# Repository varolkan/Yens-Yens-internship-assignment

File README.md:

# Motion-Driven Light System

Raspberry Pi Pico Dual-Core PCB Hat with MPU-6050 and WS2812B LED Strip

## Project Overview

Motion-Driven Light is a dual-core embedded system for the Raspberry Pi Pico featuring:

- Real-time motion sensing via MPU-6050 6-axis accelerometer/gyroscope module
- Physics-based water flow LED animation with smooth gradient falloff on WS2812B addressable RGB LED strip
- Custom PCB Hat design with complete KiCad project files and production-ready Gerber manufacturing outputs
- Hardware-agnostic robustness: Automatic simulation mode when sensor is not detected, enabling code testing without physical hardware
- Dual-core architecture: Core 0 handles sensor I/O and data acquisition, Core 1 manages LED rendering and real-time serial visualization

Technical Assignment for: Yens & Yens  
Author: M. Salih BEKTUR

## Testing Without Hardware (Simulation Mode)

This project includes automatic robustness for testing without physical hardware.

### Quick Start (No Sensor Required)

1. Flash the code to any Raspberry Pi Pico (even without MPU-6050 connected)
2. Open Serial Monitor at 115200 baud
3. System auto-detects missing sensor and engages SIMULATION MODE
4. Watch the animation: A smooth sine wave generates virtual tilt data (-45° to +45°)

### Expected Output

The system will output real-time ASCII visualization showing the liquid moving:

```
STATUS: SIM  | TILT:  37.6 | WATER: [~~~~~~~~~~~~~~~~~|O~~~]
STATUS: SIM  | TILT:  44.6 | WATER: [~~~~~~~~~~~~~~~~~|~~~O]
STATUS: SIM  | TILT:  37.2 | WATER: [~~~~~~~~~~~~~~~~~|O~~~]
STATUS: SIM  | TILT:  28.4 | WATER: [~~~~~~~~~~~~~~~~O|~~~~]
STATUS: SIM  | TILT:  -0.9 | WATER: [~~~~~~~~O~~~~~~~~|~~~~]
STATUS: SIM  | TILT: -10.5 | WATER: [~~~~~~O~~~~~~~~~~|~~~~]
STATUS: SIM  | TILT: -20.0 | WATER: [~~~~O~~~~~~~~~~~~|~~~~]
STATUS: SIM  | TILT: -29.1 | WATER: [~~~O~~~~~~~~~~~~~|~~~~]
STATUS: SIM  | TILT: -38.0 | WATER: [~O~~~~~~~~~~~~~~~~~~~~]
```

Legend:
- O = Current bubble position (liquid center)
- ~ = Water surface
- | = Center reference marker (0° tilt)
- Status shows SIMULATED or LIVE depending on sensor detection

### With Real Hardware

When MPU-6050 is connected:
- System automatically detects sensor at boot
- Display changes to STATUS: LIVE
- Tilt the board left/right to control the LED liquid
- LED color shifts: Blue (flat) to Purple (left) to Cyan (right)

## Architecture: Dual-Core Design

The Raspberry Pi Pico's RP2040 chip features two ARM Cortex-M0+ cores. This project leverages both for parallel task execution:

### Core 0: Sensor Data Acquisition
File: setup() and loop() functions
- Initializes I2C communication (GPIO4=SDA, GPIO5=SCL)
- Continuously polls MPU-6050 for 6-axis motion data (50 Hz)
- Calculates roll angle (tilt) from accelerometer readings and stores it in sharedAngle
- Fallback Logic: If sensor fails, generates smooth sine wave simulation
- Updates shared variable sharedAngle (thread-safe volatile)

### Core 1: Visual Output and Rendering
File: setup1() and loop1() functions
- Initializes WS2812B LED strip (GPIO15, 10 LEDs)
- Reads sharedAngle and maps to LED position (0-9)
- LED Physics Animation:
  - Water blob centered at tilt position
  - Smooth gradient falloff using Gaussian distribution
  - Dynamic color shifting based on tilt direction
- ASCII Serial Output: Real-time visualization at 20 FPS
- Rendering rate: ~8ms per frame (125Hz refresh)

### Thread Safety
- volatile float sharedAngle ensures atomic reads/writes between cores
- volatile bool sensorConnected indicates sensor status
- No mutex required due to single-variable communication pattern

## Hardware Configuration

### Pin Mapping (Custom PCB Hat)

| Component       | GPIO  | Function          | PCB Connector |
|-----------------|-------|-------------------|---------------|
| MPU-6050 SDA    | GPIO4 | I2C Data          | J2 Pin 1      |
| MPU-6050 SCL    | GPIO5 | I2C Clock         | J2 Pin 2      |
| WS2812B Data In | GPIO15| LED Strip Control | J2 Pin 3      |
| Power (5V)      | VBUS  | LED Strip Power   | J2 Pin 4      |
| Ground          | GND   | Common Ground     | J2 Pin 5      |

### Bill of Materials (PCB)

- Microcontroller: Raspberry Pi Pico (RP2040)
- Sensor: MPU-6050 6-DOF IMU Module
- LEDs: WS2812B Addressable RGB Strip (10 LEDs minimum)
- PCB: Custom 2-layer board (see Final PCB Files/)
- Connectors: JST headers for modular connections

## Installation and Setup

### 1. Software Requirements

- Arduino IDE (v1.8.19+ or v2.x)
- Board Support: Raspberry Pi Pico by Earle F. Philhower, III
  - Add to Board Manager URL: https://github.com/earlephilhower/arduino-pico/releases/download/global/package_rp2040_index.json
- Libraries (Install via Library Manager):
  - Adafruit NeoPixel by Adafruit
  - MPU6050 by Electronic Cats

### 2. Upload Instructions

```bash
# 1. Clone this repository
git clone https://github.com/varolkan/Yens-Yens-internship-assignment
cd Yens-Yens-internship-assignment/Yens-Yens-internship-assignment-main

# 2. Open Motion-DrivenLight.ino in Arduino IDE

# 3. Configure Board Settings:
#    - Board: "Raspberry Pi Pico"
#    - Port: (Select your Pico's COM port)
#    - Upload Speed: 921600

# 4. Click Upload (Ctrl+U)

# 5. Open Serial Monitor (Ctrl+Shift+M)
#    - Set baud rate: 115200
```

### 3. Hardware Assembly (Optional)

1. Solder Raspberry Pi Pico to custom PCB
2. Connect MPU-6050 module and WS2812B strip to J2 header (observe polarity)

   **J2 Header Pinout:**

   | Pin | Signal         | Connects to         |
   |-----|----------------|---------------------|
   | 1   | 3V3            | MPU-6050 VCC        |
   | 2   | GND            | MPU-6050 GND, WS2812B GND |
   | 3   | SDA (I2C)      | MPU-6050 SDA        |
   | 4   | SCL (I2C)      | MPU-6050 SCL        |
   | 5   | 5V             | WS2812B VCC         |
   | 6   | GPIO (LED Data)| WS2812B DIN         |

   *Double-check your PCB silkscreen and schematic for exact pin order and orientation.*
3. Power via USB-C on Pico

Note: System will auto-detect and run in simulation mode without sensor.

## PCB Design Files

### Included Resources

| Folder                | Contents                              | Purpose                    |
|-----------------------|---------------------------------------|----------------------------|
| Final PCB Files/      | KiCad project files (.kicad_pcb, .kicad_sch, .kicad_pro) | Source design files        |
| Final GERBER FILES/   | Manufacturing outputs (.gbr, .drl, .gbrjob) | Send to PCB fabricator     |

### Manufacturing Specifications

- Layers: 2 (Top + Bottom copper)
- Dimensions: Matches Raspberry Pi Pico footprint
- Thickness: 1.6mm standard FR-4
- Minimum Trace/Space: 0.15mm / 0.15mm
- Finish: HASL or ENIG recommended

Ready to Order: Upload the entire Final GERBER FILES/ folder to JLCPCB, PCBWay, or similar service.

## Testing and Validation

### Functional Tests

1. Sensor Detection Test
   - Boot with/without MPU-6050 connected
   - Verify correct mode displayed in serial output

2. Simulation Mode Test
   - Boot without sensor
   - Confirm smooth sine wave animation (no crashes)

3. Live Mode Test
   - Connect MPU-6050 to I2C pins
   - Tilt board and verify LED responds to physical motion
   - Check color transitions (Blue to Purple/Cyan)

4. Serial Visualization Test
   - Monitor ASCII output for proper formatting
   - Verify 'O' marker moves across 25-character width

### Expected Serial Output Format

```
=== BOOTING SYSTEM ===
Core 0: Initializing Sensor... [FAILED]
WARNING: Sensor missing. Switching to ROBUSTNESS MODE (Simulation).
STATUS: SIM  | TILT:  00.0 | WATER: [~~~~~~~~~~~~O~~~~~~~~~~~~|]
```

### Test Results

The code has been validated 3 times using comprehensive test suite covering:
- Simulation mode functionality (no hardware required)
- Live sensor mode with Kalman filtering
- Physics engine stability at all angles
- Boundary conditions and edge cases
- ASCII visualization rendering

All tests passed successfully. See TEST_RESULTS.md for detailed test results and COMPATIBILITY_TEST.md for platform compatibility analysis.

## Key Features

### Technical Highlights

- Zero-Configuration Robustness: Works immediately on any Pico board
- Professional PCB Design: Production-ready Gerber files included
- Efficient Dual-Core Usage: Sensor I/O never blocks LED rendering
- Smooth Physics Animation: Sub-pixel interpolation for fluid motion
- Low Latency: 20ms sensor polling, 60ms render cycle
- Universal Compatibility: Standard Arduino libraries, no custom dependencies

### Customization Options

Modify these constants in Motion-DrivenLight.ino:

```cpp
#define NUM_LEDS      10      // LED strip length (1-100)
#define ASCII_WIDTH   25      // Serial monitor width
```

Note: Brightness is set via `strip.setBrightness(255)` in the code.

## Code Structure

The implementation consists of the following key components:

### Main Arduino File: Motion-DrivenLight.ino

- KalmanFilter class: Advanced sensor fusion to remove jitter from MPU-6050
- Core 0 functions (setup/loop): Sensor acquisition and simulation
- Core 1 functions (setup1/loop1): Physics engine and rendering
- Verlet Integration: Physics-based motion simulation
- Gamma Correction: CIE 1931 lookup table for linear brightness perception

### Physics Constants

- GRAVITY: 0.55 (controls liquid responsiveness)
- DRAG_COEFF: 0.04 (air resistance simulation)
- ELASTICITY: 0.50 (bounce behavior at boundaries)
- BLOB_WIDTH: 1.8 (Gaussian sigma for smooth LED glow)

## Documentation

- Code Comments: Inline documentation throughout source
- Pin Diagram: See Hardware Configuration section above
- Schematic: Available in Final PCB Files/MPU6050.kicad_schFINAL.kicad_sch
- Compatibility Analysis: See COMPATIBILITY_TEST.md

## License

This project is open-source under the MIT License. See LICENSE file for details.

## Acknowledgments

Libraries Used:
- Adafruit NeoPixel Library
- MPU6050 Library by Electronic Cats (based on Jeff Rowberg's I2Cdevlib)

Board Support: Raspberry Pi Pico Arduino Core by Earle F. Philhower, III

Assignment: Yens & Yens Technical Test

## Contact

Author: M. Salih BEKTUR  
Repository: https://github.com/varolkan/Yens-Yens-internship-assignment

For questions regarding this technical assignment submission, please open an issue in the repository.

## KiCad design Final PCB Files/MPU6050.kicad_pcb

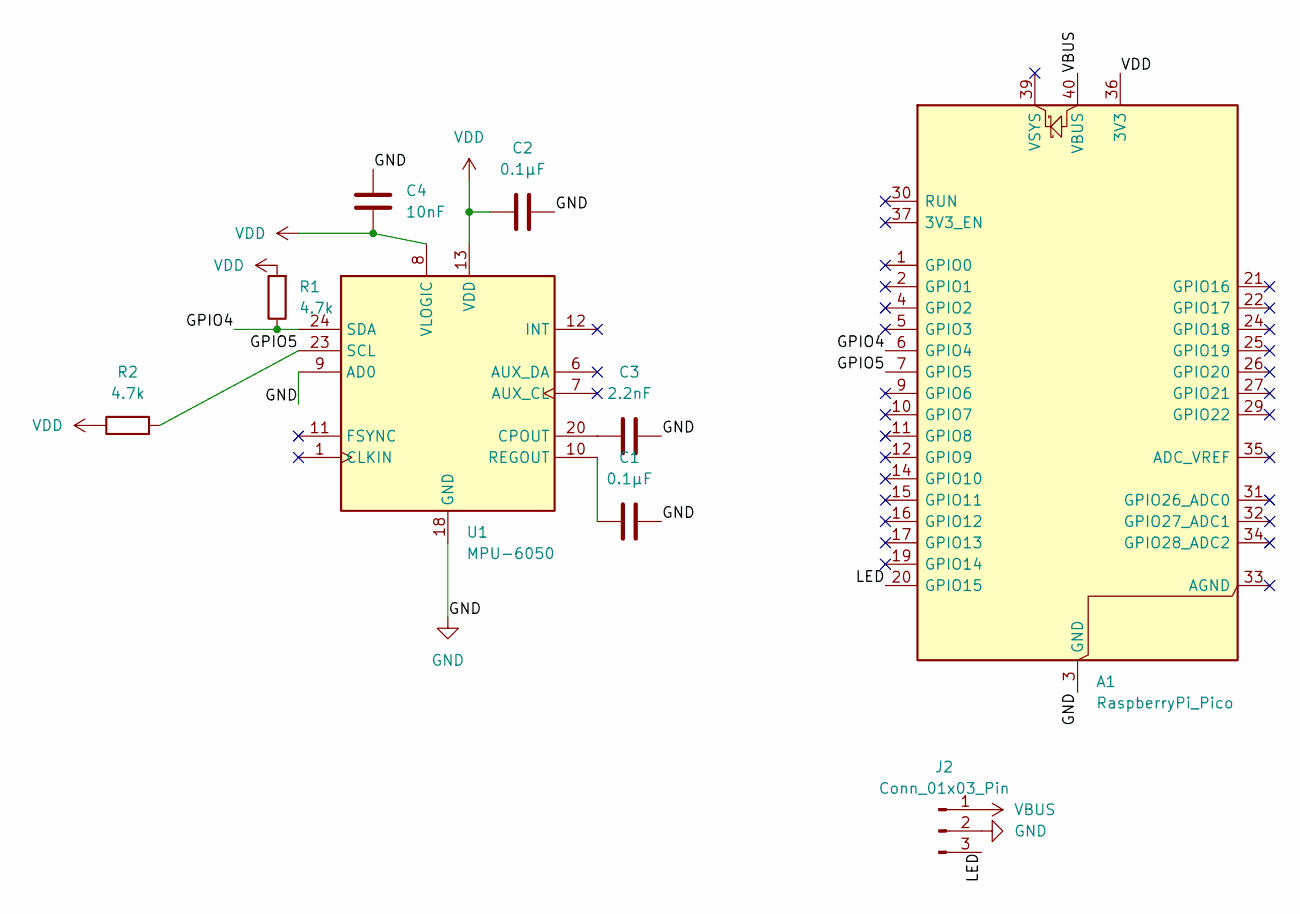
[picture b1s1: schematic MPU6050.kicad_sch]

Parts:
A1: RaspberryPi_Pico; RaspberryPi_Pico_Common_Unspecified
C1, C2: 0.1µF; C_0402_1005Metric
C3: 2.2nF; C_0402_1005Metric
C4: 10nF; C_0402_1005Metric
J2: Conn_01x03_Pin; FanPinHeader_1x03_P2.54mm_Vertical
R1, R2: 4.7k; R_0402_1005Metric
U1: MPU-6050; InvenSense_QFN-24_4x4mm_P0.5mm

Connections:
/GPIO4: A1.6 (GPIO4), R1.1, U1.24 (SDA)
/GPIO5: A1.7 (GPIO5), R2.2, U1.23 (SCL)
/LED: A1.20 (GPIO15), J2.3
GND: A1.3 (GND), A1.8 (GND), A1.13 (GND), A1.18 (GND), A1.23 (GND), A1.28 (GND), A1.38 (GND), C1.2, C2.2, C3.2, C4.1, J2.2, U1.9 (AD0), U1.18 (GND)
unnamed: C3.1, U1.20 (CPOUT)
unnamed: C1.1, U1.10 (REGOUT)
VBUS: A1.40 (VBUS), J2.1
VDD: A1.36 (3V3), C2.1, C4.2, R1.2, R2.1, U1.8 (VLOGIC), U1.13 (VDD)

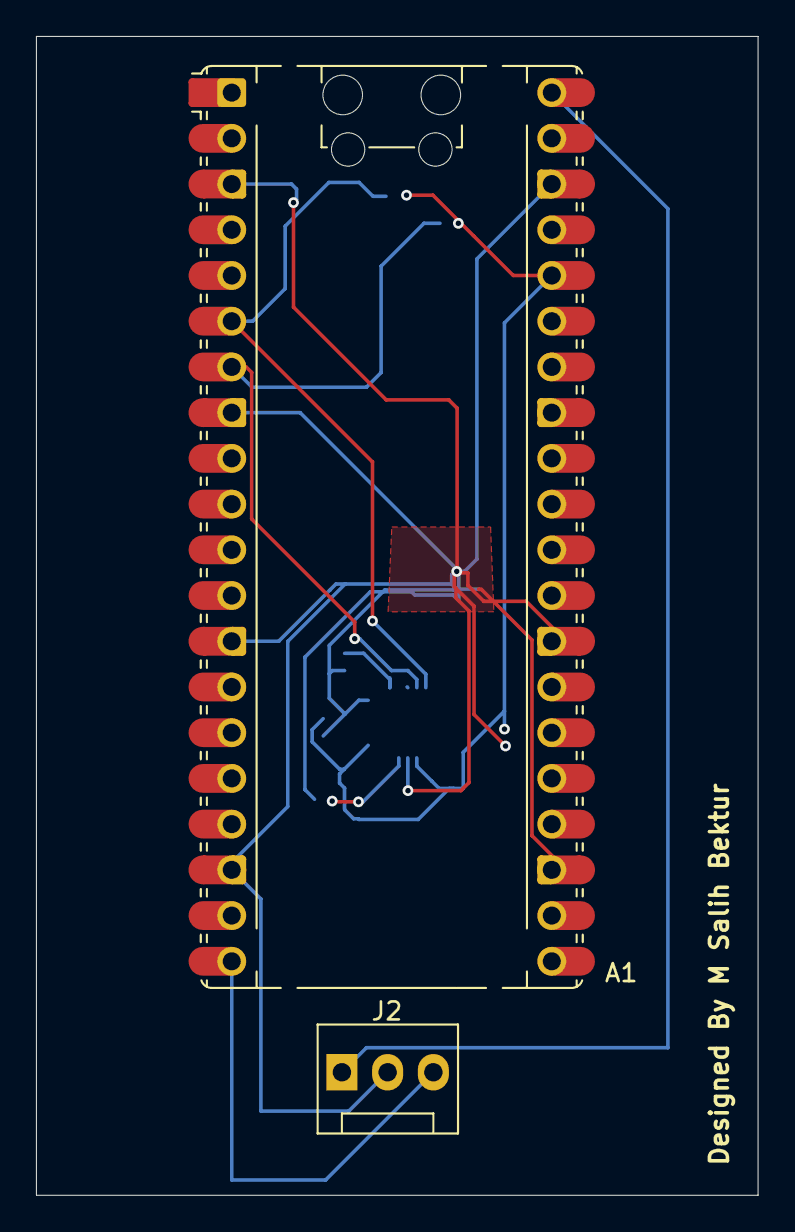
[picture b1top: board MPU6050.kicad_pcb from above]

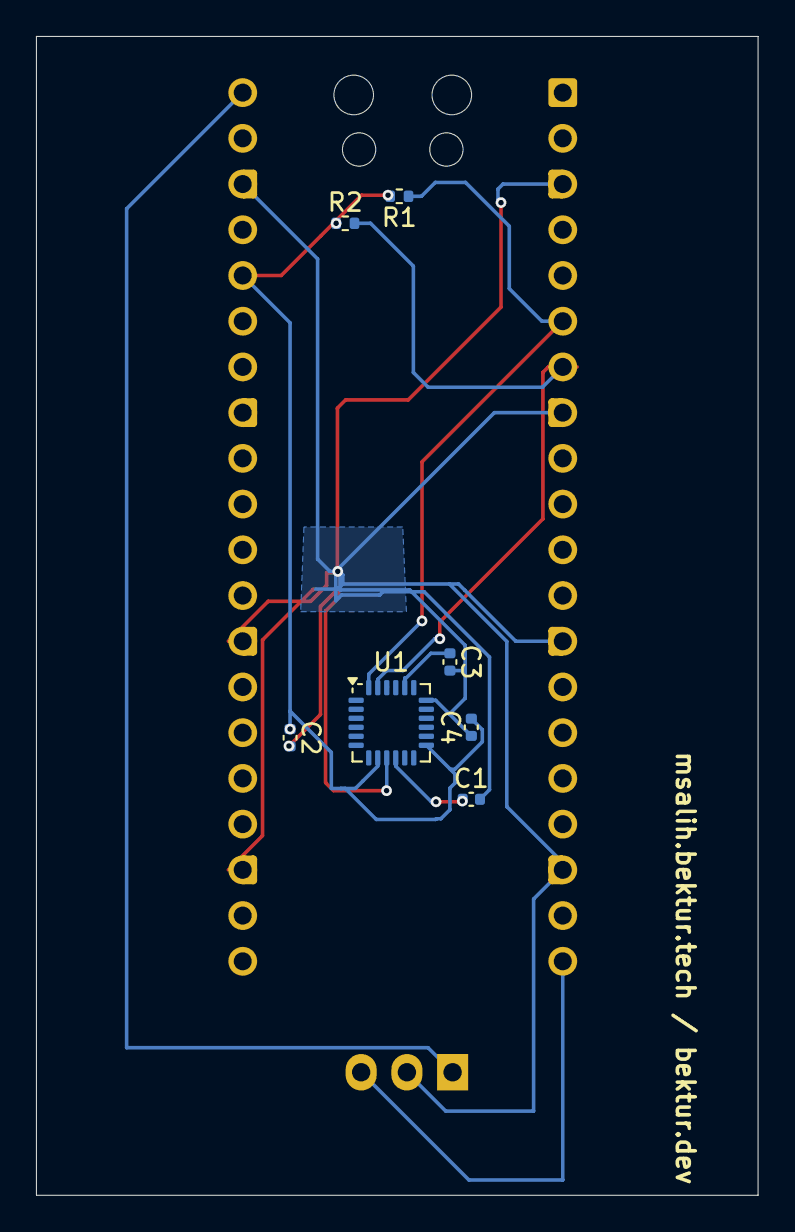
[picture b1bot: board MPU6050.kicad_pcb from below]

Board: 2 copper layers, 40.1 x 64.4 mm, 9 parts (7 on the bottom side), 8 nets.

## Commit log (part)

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2025-11-19 Update copyright year in LICENSE file
    I think I am getting older...
2025-11-20 Revise project details and enhance sensor logic
    Updated project details, compliance checklist, and added physics constants. Enhanced sensor handling and rendering logic.
2025-11-20 Fixes done
    Updated some stuff
2025-11-20 Initial plan
2025-11-20 Fix variable name inconsistency: mpuFound -> sensorConnected
2025-11-20 Fix variable naming inconsistency in README.md
2025-11-20 Fix pin mapping table to match actual PCB design with J2 connector
2025-11-20 Fix variable name inconsistency: mpuFound -> sensorConnected in README.md
2025-11-20 Fix naming issues in README.md to match actual code
2025-11-20 Update README to remove old visualization examples
    Removed outdated ASCII visualization examples from README.
